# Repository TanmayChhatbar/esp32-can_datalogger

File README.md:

# ESP32-based CAN Datalogger

https://github.com/user-attachments/assets/50ae6a31-43c1-45fb-a447-b922d48a3503

[More information on YouTube](https://youtu.be/qLKWpdkve9A)

## Idea

- Overall datalogger using CAN
- One CAN for/from the motorcycle, one for/from sensors
- Request signals over OBD from the motorcycle
- Onboard GPS for location and time
- Onboard IMU
- External antenna
- Onboard button cell for hot-starts
- TPMS (for BLE-based sensors)

## Hardware

| Utility           | Component          |
| ----------------- | ------------------ |
| Microcontroller   | ESP32-C6 Supermini |
| CAN Transceiver   | TJA1051 (x2)       |
| SD card connector | MSD-4-A            |
| IMU               | ICM-20948          |
| GPS               | PA-1616D           |

## References

- [cantools](https://github.com/cantools/cantools)
- [MT07_CAN_Project](https://github.com/JackHat1/MT07_CAN_Project)

## Future Work (Suggest)

- Super-capacitor for saving logs on sudden power-cut?
- Revise mounting for reducing engine vibration
- Improved GPS chip

  | Chip                                                                                             | Features                        | Cost  |
  | ------------------------------------------------------------------------------------------------ | ------------------------------- | ----- |
  | [Quectel LC29HCA](https://forums.quectel.com/uploads/short-url/nu6XgBFKtXOYPPegStMeuTfr7L9.pdf)  | dual band, 10hz, DR             | 24.69 |
  | [Quectel LC29HBA](https://forums.quectel.com/uploads/short-url/nu6XgBFKtXOYPPegStMeuTfr7L9.pdf)  | dual band, 10hz, DR, RTK        | 42.73 |
  | [NEO-M9V](https://content.u-blox.com/sites/default/files/NEO-M9V-20B_DataSheet_UBX-21029781.pdf) | single-band, 50hz (with DR), DR | 18.67 |

- Improved IMU

  | Chip                                                                                                                             | Features                   | Cost  |
  | -------------------------------------------------------------------------------------------------------------------------------- | -------------------------- | ----- |
  | [BNO086](https://www.digikey.com/en/products/detail/ceva-technologies-inc/BNO086/14114190)                                       | Updated from 085   | 13.93 |
  | [ICM-45686](https://www.digikey.com/en/products/detail/tdk-invensense/icm-45686/24374985)                                        | TODO               | 5.26  |
  | [IAM-20680HP](https://www.digikey.com/en/products/detail/tdk-invensense/IAM-20680HP/13419974)                                    | Automotive, TODO   | 15.88 |

- Standalone Magnetometer

  | Chip                                                                                                                                                                                                                                                                                                                                                                                                                                         | Features | Cost |
  | -------------------------------------------------------------------------------------------------------------------------------------------------------------------------------------------------------------------------------------------------------------------------------------------------------------------------------------------------------------------------------------------------------------------------------------------- | -------- | ---- |
  | [List](https://www.digikey.com/en/products/filter/magnetic-sensors/linear-compass-ics/554?s=N4IgjCBcoGwJxVAYygMwIYBsDOBTANCAPZQDaIALAAxwDMdIAuoQA4AuUIAymwE4CWAOwDmIAL6EATGBiIQKSBhwFiZcCEIVJk2lQjMQ7TjwEjxUgOyzo8tFjyESkcmEkWaEQq4tgZG8JIAHBYWtP6uwXBU4bpBFP4ArIG0YGGESdKBiXAJIYnwevm0CZIxugmyXrTlFjEwkjDRVfUWCFUWFPThFpJUFf69SXCVIDAUYD2lUlSB8G0gvcHSTKwckNx8QqIS4HCBCDYKSg6qziDRjDsAtKWHUHwAripO5AlMYjvWoPwAJpxXYEKq04-jYAE8WLhOD9sCgPkA) | To check | 0.0  |

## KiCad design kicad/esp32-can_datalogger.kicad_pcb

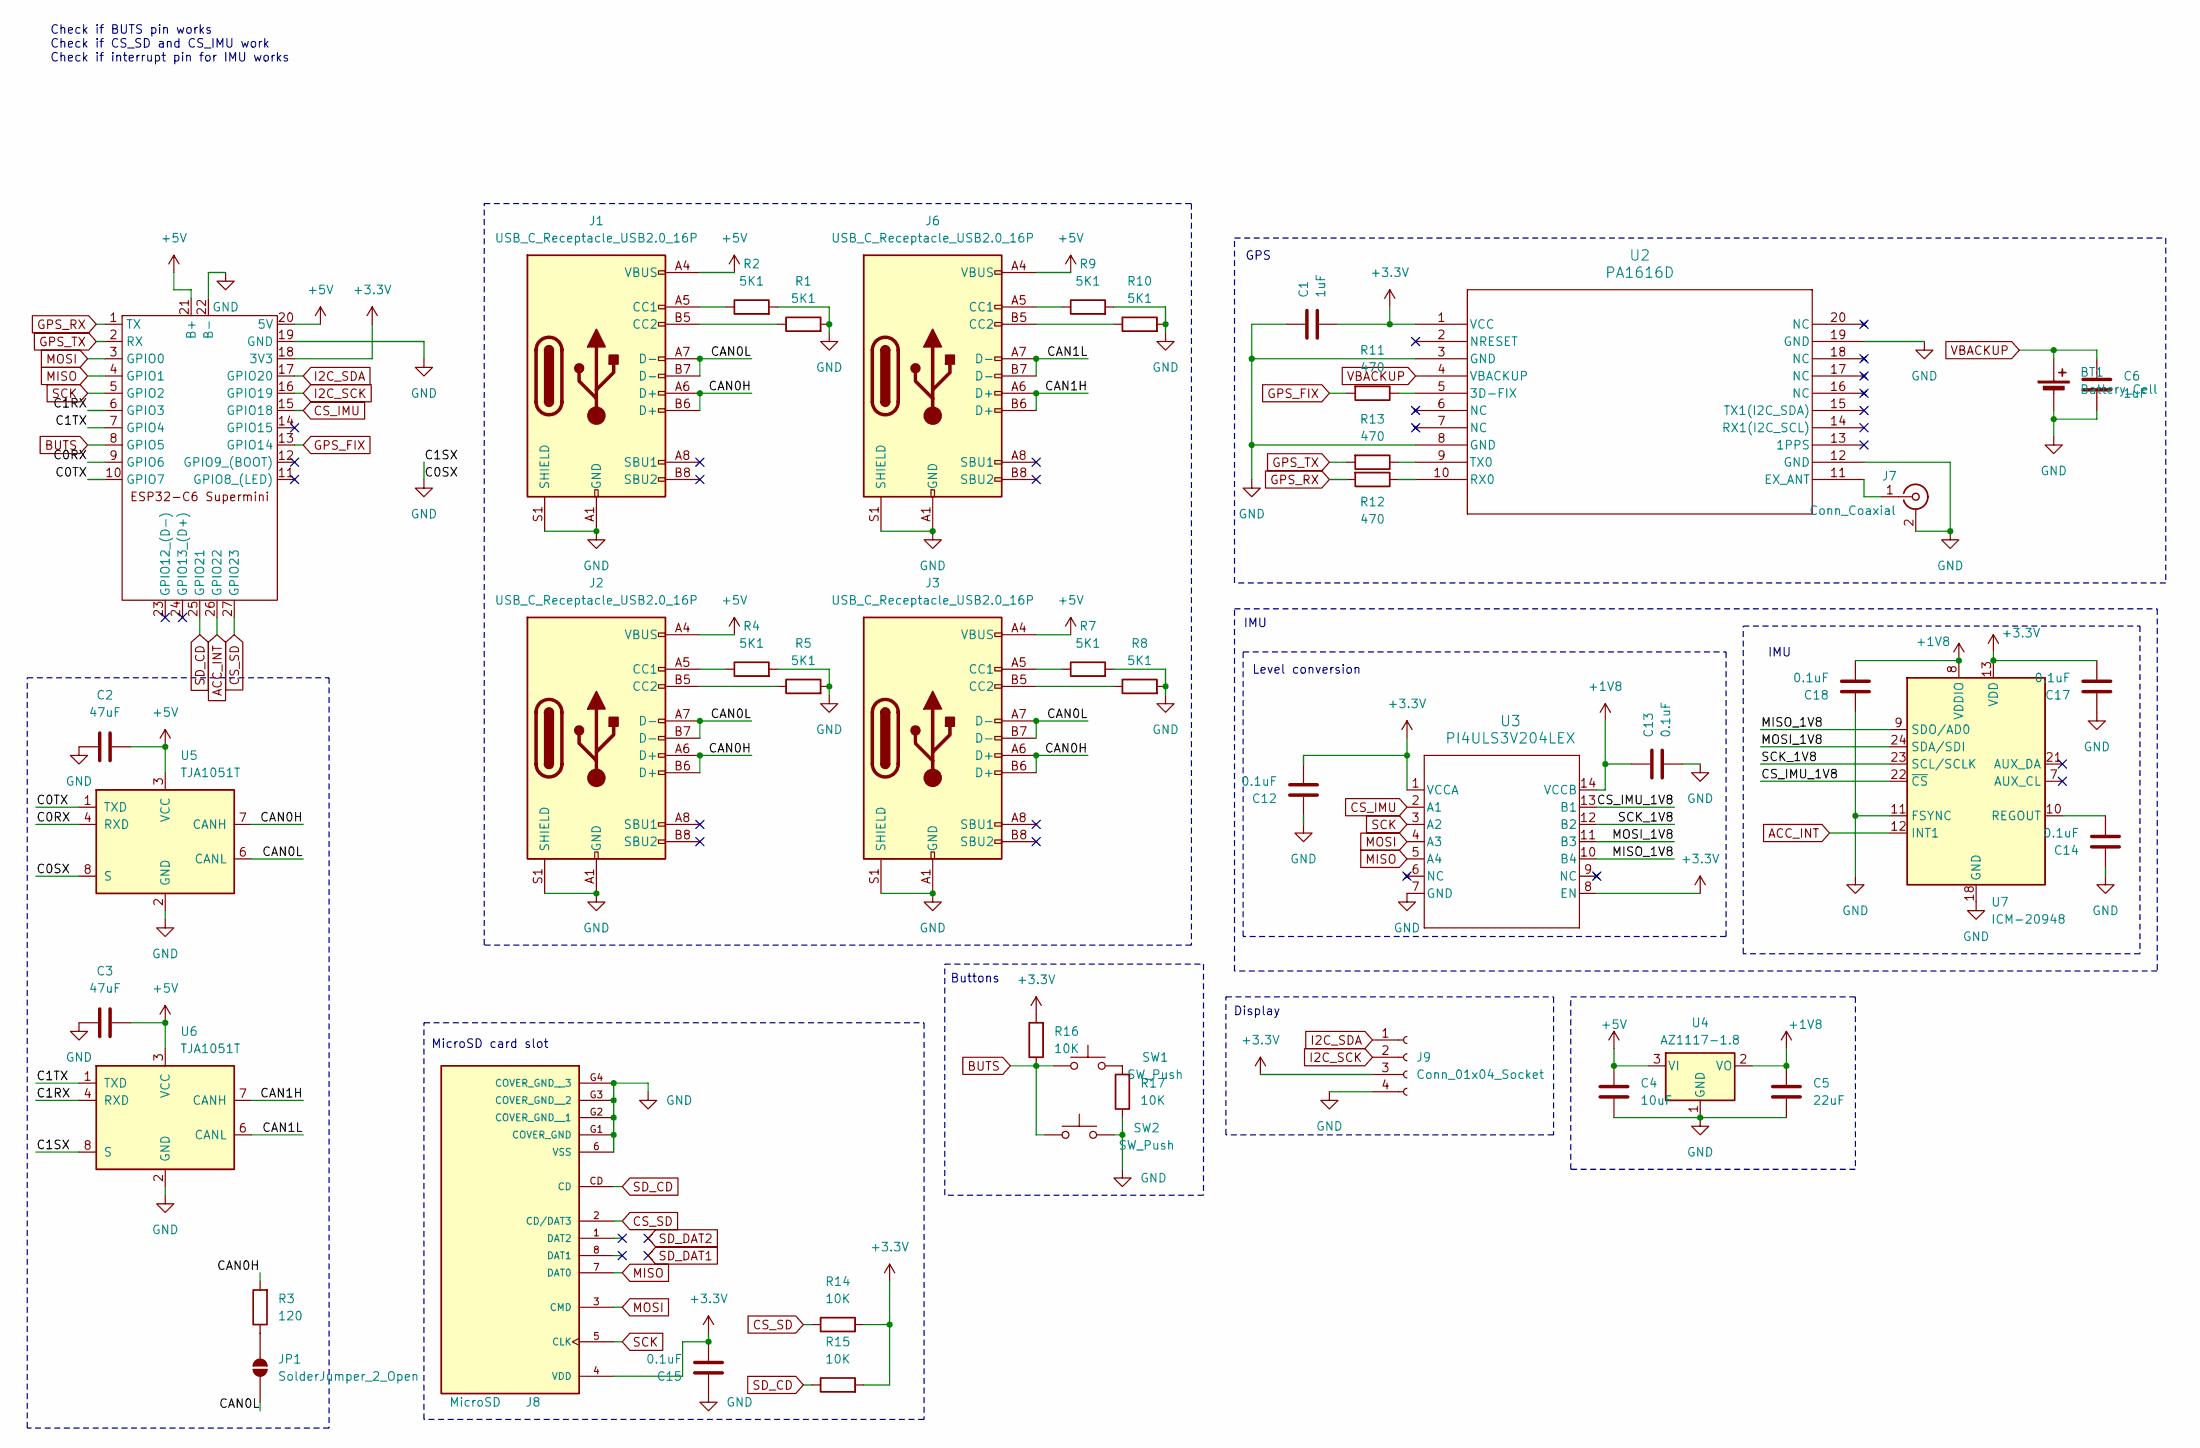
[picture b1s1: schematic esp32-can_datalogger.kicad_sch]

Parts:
BT1: Battery_Cell; BAT_1056
C1, C6: 1uF; C_0402_1005Metric_Pad0.74x0.62mm_HandSolder
C2, C3: 47uF; C_1206_3216Metric_Pad1.33x1.80mm_HandSolder
C4: 10uF; C_1206_3216Metric_Pad1.33x1.80mm_HandSolder
C5: 22uF; C_1206_3216Metric_Pad1.33x1.80mm_HandSolder
C12, C13, C14, C15, C17, C18: 0.1uF; C_0402_1005Metric_Pad0.74x0.62mm_HandSolder
J1, J2, J3, J6: USB_C_Receptacle_USB2.0_16P; USB_C_Receptacle_GCT_USB4110-grounded shield
J7: Conn_Coaxial; SMA_BAT_Wireless_BWSMA-KWE-Z001
J8: MicroSD; CUI_MSD-4-A; PARTREV 1.0
J9: Conn_01x04_Socket; PinSocket_1x04_P2.54mm_Vertical
JP1: SolderJumper_2_Open; SolderJumper-2_P1.3mm_Open_TrianglePad1.0x1.5mm
R1, R2, R4, R5, R7, R8, R9, R10: 5K1; R_0402_1005Metric_Pad0.72x0.64mm_HandSolder
R3: 120; R_0402_1005Metric_Pad0.72x0.64mm_HandSolder
R11, R12, R13: 470; R_0402_1005Metric_Pad0.72x0.64mm_HandSolder
R14, R15, R16, R17: 10K; R_0402_1005Metric_Pad0.72x0.64mm_HandSolder
SW1, SW2: SW_Push; SW_Push_SPST_NO_Alps_SKRK
U1: ESP32-C6 Supermini
U2: PA1616D; CD-PA1616D_ADA
U3: PI4ULS3V204LEX; SOIC_3V204LEX_DIO
U4: AZ1117-1.8; SOT-223-3_TabPin2
U5, U6: TJA1051T; SOIC-8_3.9x4.9mm_P1.27mm
U7: ICM-20948; InvenSense_QFN-24_3x3mm_P0.4mm

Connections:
+1V8: C5.1, C13.1, C18.2, U3.14 (VCCB), U4.2 (VO), U7.8 (VDDIO)
+3.3V: C1.2, C12.2, C15.2, C17.2, J8.4 (VDD), J9.3, R14.2, R15.2, R16.2, U1.18 (3V3), U2.1 (VCC), U3.1 (VCCA), U3.8 (EN), U7.13 (VDD)
+5V: C2.2, C3.2, C4.1, J1.A4 (VBUS), J1.A9 (VBUS), J1.B4 (VBUS), J1.B9 (VBUS), J2.A4 (VBUS), J2.A9 (VBUS), J2.B4 (VBUS), J2.B9 (VBUS), J3.A4 (VBUS), J3.A9 (VBUS), J3.B4 (VBUS), J3.B9 (VBUS), J6.A4 (VBUS), J6.A9 (VBUS), J6.B4 (VBUS), J6.B9 (VBUS), U1.20 (5V), U1.21 (B+), U4.3 (VI), U5.3 (VCC), U6.3 (VCC)
/C0RX: U1.9 (GPIO6), U5.4 (RXD)
/C0TX: U1.10 (GPIO7), U5.1 (TXD)
/C1RX: U1.6 (GPIO3), U6.4 (RXD)
/C1TX: U1.7 (GPIO4), U6.1 (TXD)
/CAN0H: J1.A6 (D+), J1.B6 (D+), J2.A6 (D+), J2.B6 (D+), J3.A6 (D+), J3.B6 (D+), R3.2, U5.7 (CANH)
/CAN0L: J1.A7 (D-), J1.B7 (D-), J2.A7 (D-), J2.B7 (D-), J3.A7 (D-), J3.B7 (D-), JP1.1 (A), U5.6 (CANL)
/CAN1H: J6.A6 (D+), J6.B6 (D+), U6.7 (CANH)
/CAN1L: J6.A7 (D-), J6.B7 (D-), U6.6 (CANL)
/CS_IMU_1V8: U3.13 (B1), U7.22 (~CS)
/MISO_1V8: U3.10 (B4), U7.9 (SDO/AD0)
/MOSI_1V8: U3.11 (B3), U7.24 (SDA/SDI)
/SCK_1V8: U3.12 (B2), U7.23 (SCL/SCLK)
ACC_INT: U1.26 (GPIO22), U7.12 (INT1)
BUTS: R16.1, SW1.1, SW2.1, U1.8 (GPIO5)
CS_IMU: U1.15 (GPIO18), U3.2 (A1)
CS_SD: J8.2 (CD/DAT3), R14.1, U1.27 (GPIO23)
GND: BT1.2 (-), C1.1, C2.1, C3.1, C4.2, C5.2, C6.2, C12.1, C13.2, C14.1, C15.1, C17.1, C18.1, J1.A1 (GND), J1.A12 (GND), J1.B1 (GND), J1.B12 (GND), J1.S1 (SHIELD), J2.A1 (GND), J2.A12 (GND), J2.B1 (GND), J2.B12 (GND), J2.S1 (SHIELD), J3.A1 (GND), J3.A12 (GND), J3.B1 (GND), J3.B12 (GND), J3.S1 (SHIELD), J6.A1 (GND), J6.A12 (GND), J6.B1 (GND), J6.B12 (GND), J6.S1 (SHIELD), J7.2 (Ext), J8.6 (VSS), J8.G1 (COVER_GND), J8.G2 (COVER_GND__1), J8.G3 (COVER_GND__2), J8.G4 (COVER_GND__3), J9.4, R1.2, R2.2, R4.2, R5.2, R7.2, R8.2, R9.2, R10.2, R17.1, SW2.2, U1.19 (GND), U1.22 (B-), U2.3 (GND), U2.8 (GND), U2.12 (GND), U2.19 (GND), U3.7 (GND), U4.1 (GND), U5.2 (GND), U5.8 (S), U6.2 (GND), U6.8 (S), U7.11 (FSYNC), U7.18 (GND), U7.20 (GND)
GPS_FIX: R11.2, U1.13 (GPIO14)
GPS_RX: R12.2, U1.1 (TX)
GPS_TX: R13.2, U1.2 (RX)
I2C_SCK: J9.2, U1.16 (GPIO19)
I2C_SDA: J9.1, U1.17 (GPIO20)
MISO: J8.7 (DAT0), U1.4 (GPIO1), U3.5 (A4)
MOSI: J8.3 (CMD), U1.3 (GPIO0), U3.4 (A3)
unnamed: J1.A5 (CC1), R2.1
unnamed: J1.B5 (CC2), R1.1
unnamed: J2.A5 (CC1), R4.1
unnamed: J2.B5 (CC2), R5.1
unnamed: J3.A5 (CC1), R7.1
unnamed: J3.B5 (CC2), R8.1
unnamed: J6.A5 (CC1), R9.1
unnamed: J6.B5 (CC2), R10.1
unnamed: J7.1 (In), U2.11 (EX_ANT)
unnamed: JP1.2 (B), R3.1
unnamed: R17.2, SW1.2
unnamed: R11.1, U2.5 (3D-FIX)
unnamed: R12.1, U2.10 (RX0)
unnamed: R13.1, U2.9 (TX0)
unnamed: C14.2, U7.10 (REGOUT)
SCK: J8.5 (CLK), U1.5 (GPIO2), U3.3 (A2)
SD_CD: J8.CD, R15.1, U1.25 (GPIO21)
VBACKUP: BT1.1 (+), C6.1, U2.4 (VBACKUP)

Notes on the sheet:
GPS
Level conversion
IMU
Check if BUTS pin works Check if CS_SD and CS_IMU work Check if interrupt pin for IMU works
MicroSD card slot
Buttons
Display

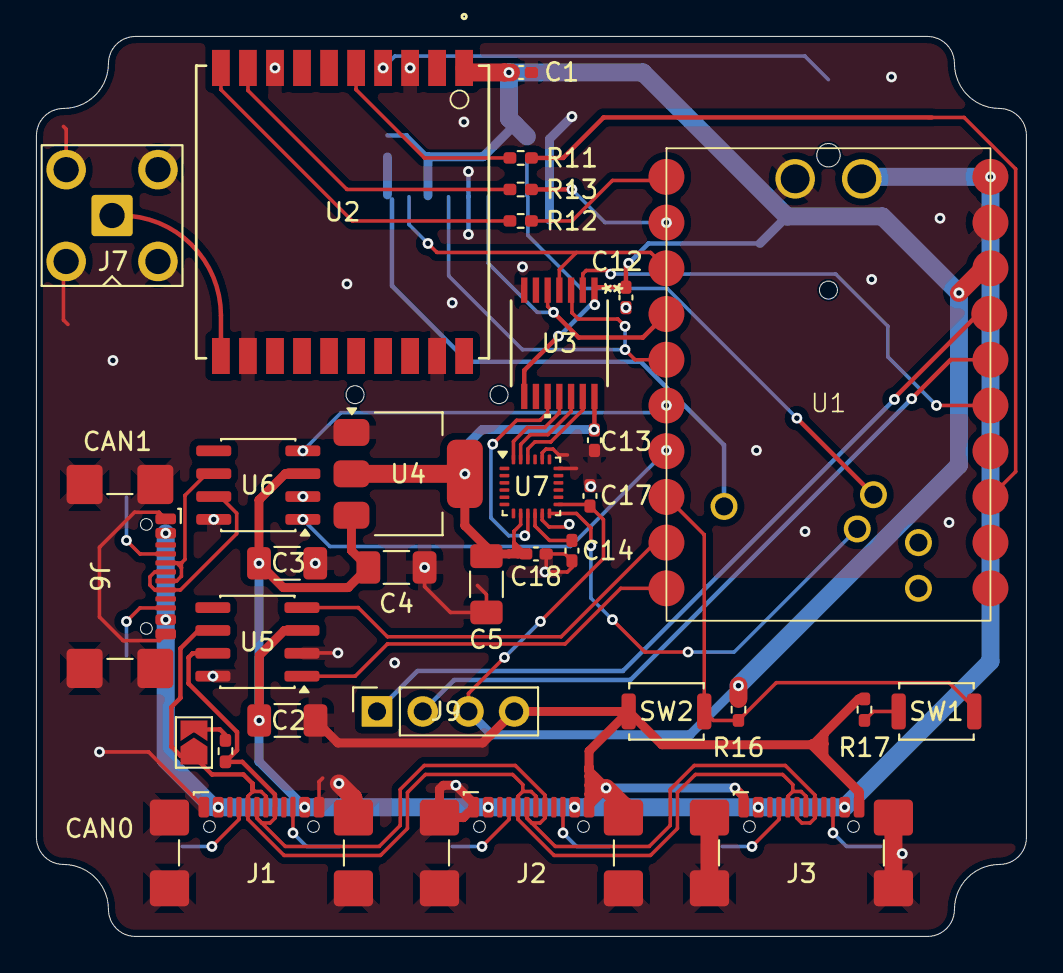
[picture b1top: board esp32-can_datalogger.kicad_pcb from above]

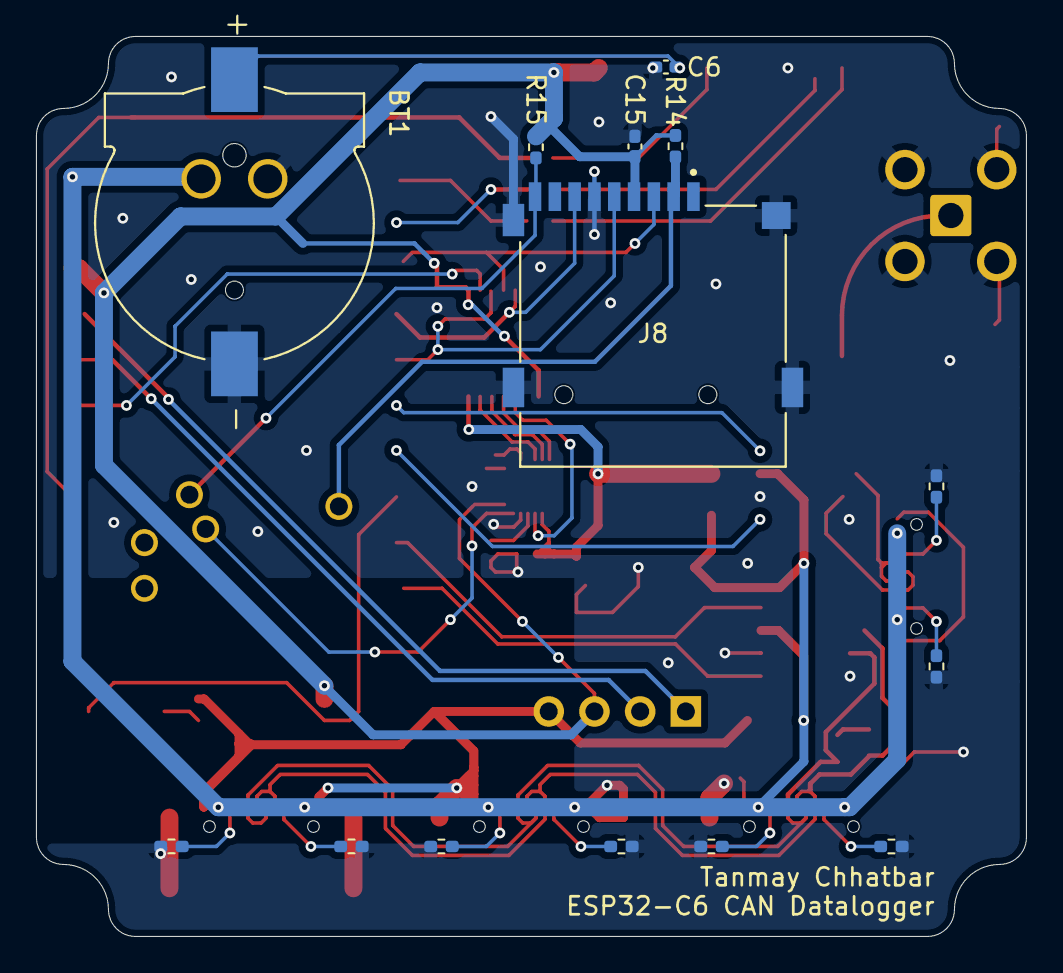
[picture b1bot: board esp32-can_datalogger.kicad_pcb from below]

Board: 2 copper layers, 55.0 x 50.0 mm, 46 parts (14 on the bottom side), 45 nets.

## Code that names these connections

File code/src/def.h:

#pragma once

// CAN
#define CAN0_TX 0
#define CAN0_RX 1
#define CAN0_SX 15
#define CAN1_TX 2
#define CAN1_RX 3
#define CAN1_SX CAN0_SX

// GPS
// #define GPS_TX TODO
// #define GPS_RX TODO
#define GPS_FIX 14

// SPI
#define MOSI 5
#define MISO 6
#define SCK 7

// IMU
#define CS_IMU 4

// SD card
#define CS_SD 18
#define SD_CD 21

// I2C
#define SDA 20
#define SCL 19
#define I2C_DISP 0x3C // TODO

// IO
#define ARGB_LED 9
#define NUM_LED 3
#define BUTS 22

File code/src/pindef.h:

#pragma once

// CAN
#define CAN0_TX 0
#define CAN0_RX 1
#define CAN0_SX 15
#define CAN1_TX 2
#define CAN1_RX 3
#define CAN1_SX CAN0_SX

// GPS
#define GPS_TX 16
#define GPS_RX 17
#define GPS_FIX 14

// SPI
#define SPI_MOSI 5
#define SPI_MISO 6
#define SPI_SCK 7

// IMU
#define SPI_CS_IMU 4

// SD card
#define SPI_CS_SD 18
#define SD_CD 21

// I2C
#define I2C_SDA 20
#define I2C_SCL 19
#define I2C_DISP 0x3C // TODO

// IO
#define ARGB_LED 8
#define NUM_LED 1
#define BUTS 22 // 22 does not support analogRead(), TODO needs PCB change. GPIO0-6 support analogRead() https://documentation.espressif.com/esp32-c6_datasheet_en.html

// voltages if BUTS is analogRead() capable
// #define BUTS_V1 
// #define BUTS_V2
// #define BUTS_V3
// #define BUTS_V4

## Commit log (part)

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2026-04-19 init code for datalogger
2026-04-19 kicad init
2026-04-19 add readme
2026-06-07 experimental changes for ESP32-C6 and two CAN buses
2026-06-07 init gps, imu, sd card files
2026-06-07 switch to esp32-c6
2026-06-08 add gps, imu to board schematic
2026-06-08 add footprints, change to bidir TTL, make connections on c6
2026-06-08 pcb updates
2026-06-08 pcb update
2026-06-10 more
2026-06-12 add vreg
2026-06-14 remove DRC errors and warnings
2026-06-14 minor updates
2026-06-14 switch RX-TX for GPS
2026-06-17 modify definitions based on board design
2026-06-17 led bringup
2026-06-17 change SPI and I2C pins to remove conflict on compile
2026-06-17 rename def to pindef
2026-06-19 update project for esp32c6
2026-06-19 placeholders for GPS, IMU, SD
2026-06-19 CAN improvements for testing
2026-06-19 obd partially works
2026-06-20 add dbc, can.h restructure
2026-06-20 savvycan logs from 2025-06-19
2026-06-20 obd sequential query test
2026-06-20 savvycan frame sender defs for obd
2026-06-20 can print to serial like savvycan logs
2026-06-20 rebase
2026-06-20 matlab gear estimation trial
2026-06-20 add obd from csselectronics
2026-06-20 run1 - probably useless run2 - gear estimation through gears
2026-06-25 comment out esp32-s3 config
2026-06-25 savvycan utils. dbc, frame sender defs
2026-06-25 can and sd minor progress
2026-06-25 obd dont decode
2026-06-25 rename sd files
2026-06-25 remove partial obd dbc
2026-06-25 update R7 dbc
2026-06-25 rename sd files rebase
2026-06-26 vtask for obd requests should work
2026-06-26 IO TODO
2026-06-27 add step files for sd card reader and esp32c6
2026-06-27 export files
2026-06-27 return canbegin()
2026-06-27 TODO analogRead problem
2026-06-27 sd basic IO works
2026-06-28 maybe breaking, SD library doesnt work with GPS
2026-06-28 shift to header
2026-06-29 gps pins update
2026-06-29 gps works, get filename from gps time
2026-06-30 todo test
2026-06-30 only serial print in main
